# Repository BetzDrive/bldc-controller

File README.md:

# Getting Started
```bash
cd ~
git clone https://github.com/BetzDrive/bldc-controller.git
cd bldc-controller
sudo apt-get install gdb-multiarch python3-pip
make setup
```

### Testing
A quick way of running the full test suite is to use `make test`. This will lint and run any code testing.

### Compiling
```bash
bazel build //<bootloader or firmware>
```

### Uploading via ST-LINK
```bash
bazel run //<bootloader or firmware>:flash
```

### Debugging via ST-LINK
To debug during execution, you can attach the debugger at any time using the following code. Keep in mind this is done with a direct connection to the hardware via an ST-Link.
```bash
# First terminal (flash latest and start gdb multiarch)
bazel run //<bootloader or firmware>:flash
bazel run //<bootloader or firmware>:gdb
# Second terminal (start openocd server)
bazel run //<bootloader or firmware>:debug
```

### Upload firmware via RS485
```bash
bazel run //firmware:upload
```

### Upload bootloader via RS485
Use this with caution. If this fails and a power cycle or reboot occurs, the board will have to be programmed directly. In the case of a failed upload, disable the enumeration procedure and try again with the same board ID. To be safe, first upload and test on an easy-to-remove link such as the gripper or base which are not as difficult to access in case of a failure.

```bash
bazel run //bootloader:upload
```

### Serial Transmission Speed Limits
USB Serial device drivers only permit at most one transmission per millisecond. By default, this is set to 16 milliseconds on our usb to RS485 converters. To change this execute the following terminal commands:

```bash
cat /sys/bus/usb-serial/devices/ttyUSB<id_num>/latency_timer
setserial /dev/ttyUSB<id_num> low_latency
cat /sys/bus/usb-serial/devices/ttyUSB<id_num>/latency_timer
```

(when running the arm, this is done automatically by the ROS control stack)

# Python Scripts
These scripts are made to remotely interface with the boards. They can debug, program, and run the boards. They interface using our custom communications protocol. The scripts are grouped under the base command `bdt`. Read more with `bdt -h`.

### Motor Calibration
To calibrate the motor board, a motor must first be attached without a load for optimal calibration. The results of calibration are based on the properties of the given motor.

* `bdt calibrate_encoder <serial_port> <board_id> <duty_cycle>`
* `bdt upload_calibration <serial_port> <board_id>`

1. Run _calibrate_encoder_: for 24V Power Supplies the duty cycle used in testing is 0.3 and for 48V or 50V supplies use half (0.15). This will generate a file called calibrations.json
2. Run _upload_calibration_ with the updated calibrations.json and the generated file will be loaded onto the board.

After completing these steps, the motor should be controllable.

### Update Motor Calibration Constants (PID and Limits)
Run this script after there's a calibration on the board. Modify the contents of the script to adjust tunings!

`bdt update_calibration <serial_port> <board_id>`

### Motor Control
Use this script to spin a motor with a given current command. A substantial starting point is 0.5 and increase above this with proper supervision! A negative command will reverse the direction. Description of what arguments each mode takes can be found with the '-h' option.

`bdt control_motor <serial_port> <board_id> <mode> <command>`

To control multiple motors,

```
bdt control_motor <serial_port> 1,2,3 torque 0.5,0.25,0
bdt control_motor <serial_port> 1,2,3 current [0,0.5],[0,0.25],[0,0]
```

### Read Sensor
This script lets a user read from any of the sensors on-board the device.

`bdt read_sensor <serial_port> <board_ids> <sensor>`

### View Control Loop
Plots the control target and the resulting quadrature/direct current commands. This is low frequency so use the recorder to get a better sense of the internal state of the motor driver.

### Recording
These scripts start and read off an on-board buffer of the commutation at each control cycle. There are included plotting scripts. This interfaces directly with the Recorder class in the firmware.

# System Design
The BLDC is built on ChibiOS. The operating system allows for quick development and thread management which have been useful for this fast-paced project. To supplement missing features, the STM32 library has been included. Memory is allocated primarily for firmware though two blocks are used to store the calibration and board id (refer to section 3.3 of [reference manual](https://www.st.com/content/ccc/resource/technical/document/reference_manual/3d/6d/5a/66/b4/99/40/d4/DM00031020.pdf/files/DM00031020.pdf/jcr:content/translations/en.DM00031020.pdf "STM32F4 Reference Manual") for memory).

## Common
In both firmware and bootloader, the primary system is the communication code. This is designed to allow users to read/write variables as well as reprogram the board remotely. When a board receives a packet, a small green LED will blink to indicate it has identified the message.

## Bootloader [Flash Sector 0]
This small system is primarily meant as a method to allow updates of the firmware without a programmer. On command, it will move the program counter to the start of the firmware code.

### LED Indicator
During normal operation, the bootloader will pulse the RGB LED blue.

## Board ID [Flash Sector 1]
To keep track of the board ID when switching between firmware and bootloader, and in case of a system fault, the board id is stored in flash.

## Calibrations [Flash Sector 2]
To keep calibrations between restarts, a section of flash is reserved and loaded to/from by firmware. Once a calibration is stored, it will load on boot without host intervention. To modify the calibration, either re-calibrate the motor or use the `update_calibration.py` tool.

## Firmware [Flash Sectors 4 - 11]
The firmware code starts by initializing hardware devices and then splits into a number of threads.

### LED Indicator [low priority]
During normal operation, the firmware will pulse the RGB LED green. If a red or blue pulse is seen while in firmware, the driver chip Fault and/or OTW pins have activated. Refer to the DRV8312 datasheet for the type of fault.

### Sensor Thread [low priority]
Pulls updates from the accelerometer and temperature sensor.
  
### Communication Thread [normal priority]
Used to update motor targets and read current position, velocity, accelerometer data, temperature, etc.

### Control Thread [high priority]
Pulls updates from ADC for current/voltage measurements as well as queues reads to the absolute encoder. With this data, FOC is computed with output duty cycles to STM32 timing hardware.
  
### Independent Watchdog Thread [high priority]
Used to keep the system live while protecting from the chance of a hard fault or any other unforseen errors. When a lock-up occurs, the system will reset into bootloader which will then check the watchdog reset flag. If it is active, the bootloader will return the system to firmware mode.

# Modifying Pins
All of the code can be directly modified except for the pins (althought you can technically modify it directly too). To allow for the pin definitions and defaults to be auto-generated and easily maintained, please make any modifications in [ChibiStudio](https://osdn.net/projects/chibios/) and generate new pin files from the studio interface.

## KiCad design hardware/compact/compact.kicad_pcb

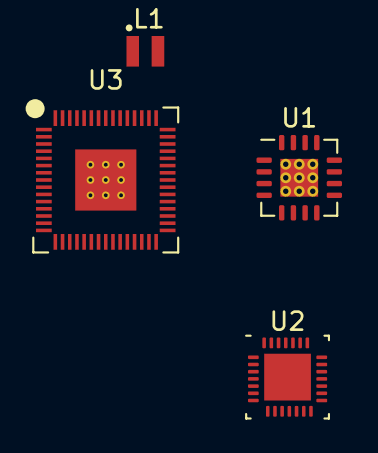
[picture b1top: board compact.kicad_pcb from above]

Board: 2 copper layers, 4 parts (0 on the bottom side), 6 nets, no tracks yet.

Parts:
L1: 3.3uH; L_pol_2016
U1: QFN-16-1EP_4x4mm_P0.65mm_EP2.1x2.1mm_ThermalVias
U2: WQFN-28-1EP_2.6x2.6mm_P0.6mm_EP2.4x2.4mm
U3: RP2350A-QFN60; RP2350A_QFN-60_EP_7.75x7.75_Pitch0.4mm

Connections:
+3V3: L1.1, U1.14 (VS), U1.15 (VS), U2.1 (PVDD), U3.1 (IOVDD), U3.6 (DVDD), U3.11 (IOVDD), U3.20 (IOVDD), U3.23 (DVDD), U3.30 (IOVDD), U3.38 (IOVDD), U3.39 (DVDD), U3.44 (ADC_AVDD), U3.45 (IOVDD), U3.46 (VREG_AVDD), U3.49 (VREG_VIN), U3.50 (VREG_FB), U3.53 (USB_OTP_VDD), U3.54 (QSPI_IOVDD)
GND: U1.6 (GND), U1.7 (GND), U2.4 (GVDD), U2.28 (GND), U3.47 (VREG_PGND), U3.61 (GND)
unnamed: U1.16 (OUT1), U3.40 (GPIO26_ADC0)
unnamed: U1.5 (OUT2), U3.41 (GPIO27_ADC1)
unnamed: U1.13 (OUT3), U3.42 (GPIO28_ADC2)
unnamed: L1.2, U3.48 (VREG_LX)

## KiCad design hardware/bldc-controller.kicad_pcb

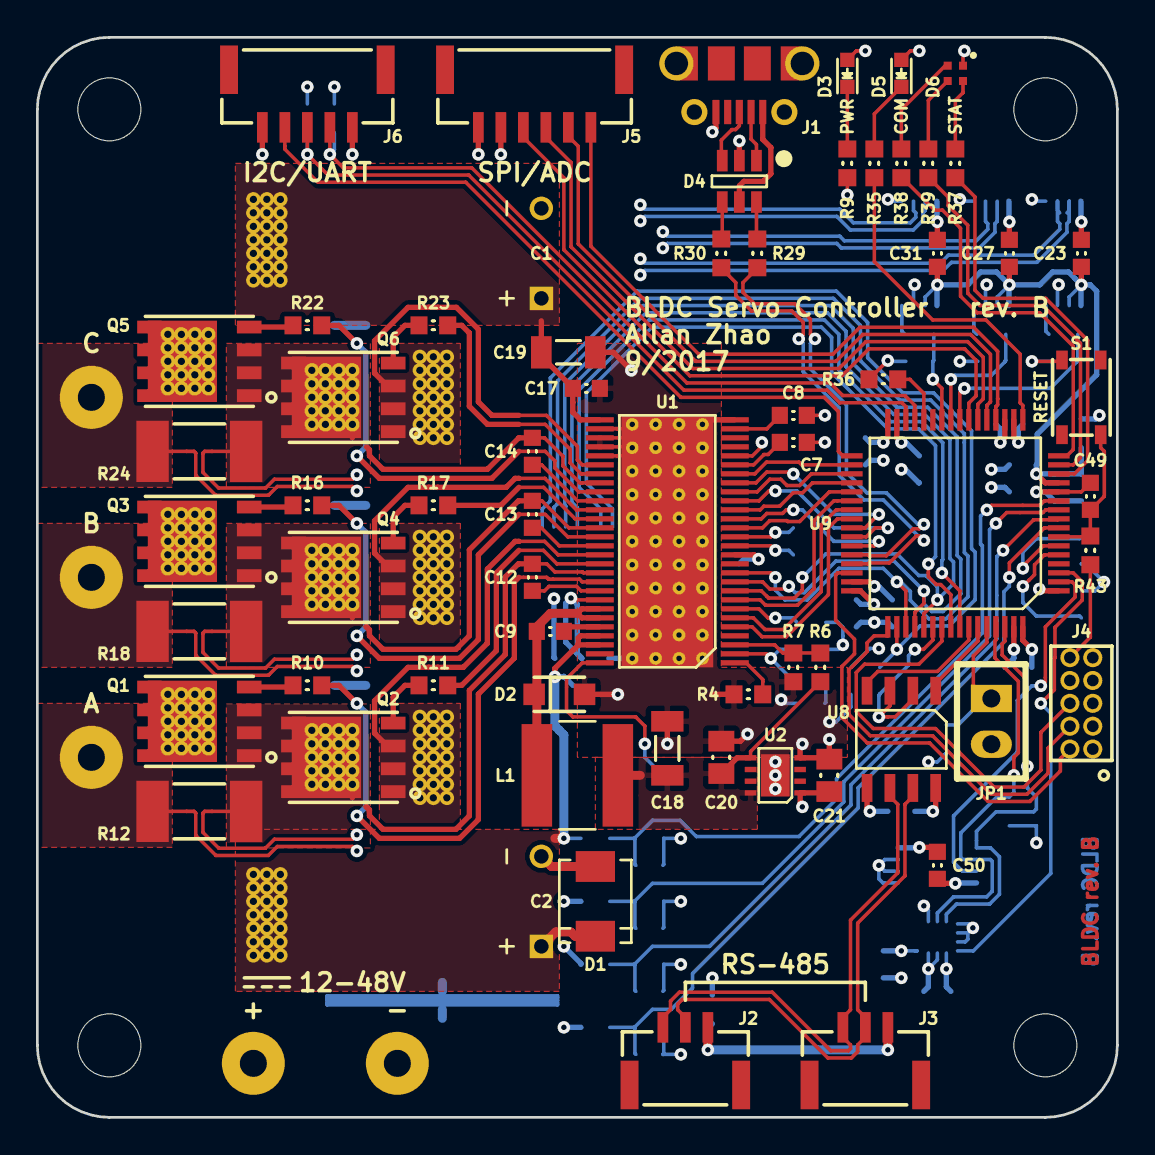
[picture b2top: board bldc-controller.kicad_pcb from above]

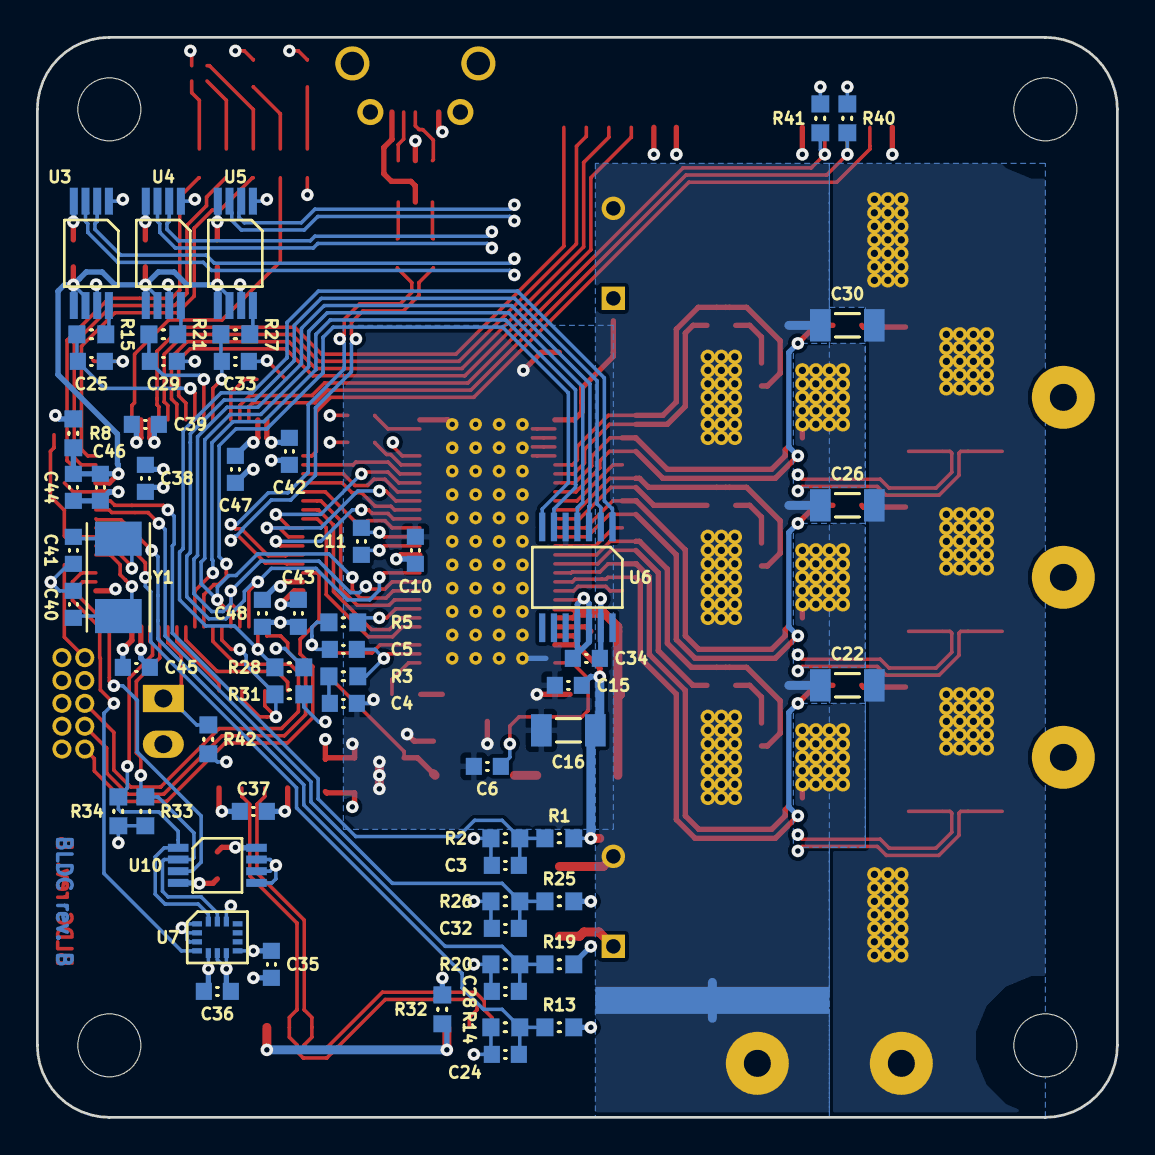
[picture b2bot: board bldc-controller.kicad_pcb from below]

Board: 4 copper layers, 60.0 x 60.0 mm, 140 parts (62 on the bottom side), 119 nets.

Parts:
C1, C2: 330u; C_Radial_D10_L26.5_P5_Horizontal
C3, C9, C12, C13, C14, C15, C17, C23, C27, C31, C34, C35, C36, C37, C39, C42, C43, C45, C46, C49, C50: 0.1u; C_0603_IPC_NOMINAL
C4: 6.8n; C_0603_IPC_NOMINAL
C5: 120p; C_0603_IPC_NOMINAL
C6: 1n; C_0603_IPC_NOMINAL
C7, C8, C44: 1u; C_0603_IPC_NOMINAL
C10, C47, C48: 2.2u; C_0603_IPC_NOMINAL
C11: 22n; C_0603_IPC_NOMINAL
C16, C19: 4.7u; C_1206_IPC_NOMINAL
C18: 47u; C_1206_IPC_NOMINAL
C20, C21: 10u; C_0805_IPC_NOMINAL
C22, C26, C30: 2.2u; C_1206_IPC_NOMINAL
C24, C28, C32: DNP; C_0603_IPC_NOMINAL
C25, C29, C33: 10n; C_0603_IPC_NOMINAL
C38: 4.7u; C_0603_IPC_NOMINAL
C40, C41: 27p; C_0603_IPC_NOMINAL
D1: SMBJ48D; DO-214AA
D2: PMEG6020ER; SOD123W
D3: Green; LED_0603
D4: ESD_DIODES; SOT23-6L
D5: Yellow; LED_0603
D6: RGB; SMLP34RGB
J1: USB_MICRO_B; 105017-0001
J2, J3: JST GH; SM03B-GHS-TB
J4: 1.27mm Pin Header; 62201021121
J5: JST GH; SM06B-GHS-TB
J6: JST GH; SM05B-GHS-TB
JP1: Pin Header; CONN-100MIL-M-1x2
L1: 33u; TYS6045
P1, P2, P3, P4, P5: Solder Terminal; SOLDER_HOLE_1.5MM
Q1, Q2, Q3, Q4, Q5, Q6: CSD18533; Q5B
R1, R13, R19, R25: 39.2k; R_0603_IPC_NOMINAL
R2, R14, R20, R26: 2.21k; R_0603_IPC_NOMINAL
R3: 15k; R_0603_IPC_NOMINAL
R4: 220k; R_0603_IPC_NOMINAL
R5, R8: 0; R_0603_IPC_NOMINAL
R6: 52.3k; R_0603_IPC_NOMINAL
R7: 10k; R_0603_IPC_NOMINAL
R9: 200; R_0603_IPC_NOMINAL
R10, R11, R16, R17, R22, R23: 4.7; R_0603_IPC_NOMINAL
R12, R18, R24: 0.002; CSS2H-2512
R15, R21, R27: 100; R_0603_IPC_NOMINAL
R28, R31, R36, R42: 47k; R_0603_IPC_NOMINAL
R29, R30: 22; R_0603_IPC_NOMINAL
R32: DNP; R_0603_IPC_NOMINAL
R33, R34, R40, R41: 4.7k; R_0603_IPC_NOMINAL
R35: 120; R_0603_IPC_NOMINAL
R37: 180; R_0603_IPC_NOMINAL
R38: 150; R_0603_IPC_NOMINAL
R39: 62; R_0603_IPC_NOMINAL
R43: 1k; R_0603_IPC_NOMINAL
S1: SW_Push_4P; PTS_810
U1: DRV8301; R-PDSO-G56-STRICT
U2: AP7361C; U-DFN3030-8
U3, U4, U5: INA240A2; TSSOP-8
U6: AS5047D; TSSOP-14
U7: LSM6DS3US; LGA-14L-STRICT
U8: ST3485; SOIC-8
U9: STM32F405R; LQFP-64
U10: LM75B; TSSOP-8
Y1: 8 MHz; ABM7
Z1: NET_TIE; WIDE_NET_TIE
Z2, Z5, Z8: NET_TIE; NET_TIE_0.3MM
Z3, Z4, Z6, Z7, Z9, Z10: NET_TIE; NET_TIE_8mil

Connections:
/Encoder/A: U6.7, U9.56
/Encoder/B: U6.6, U9.57
/Encoder/CLK: U1.11, U6.2, U9.51
/Encoder/CSN: R28.2, U6.1, U9.50
/Encoder/MISO: U1.10, U6.3, U9.52
/Encoder/MOSI: U1.9, U6.4, U9.53
/Gate Driver, Power/5V: C18.1, C20.1, L1.2, R6.1, U2.5, U2.8
/Gate Driver, Power/EN_GATE: U1.16, U9.37
/Gate Driver, Power/INH_A: U1.17, U9.43
/Gate Driver, Power/INH_B: U1.19, U9.42
/Gate Driver, Power/INH_C: U1.21, U9.41
/Gate Driver, Power/INL_A: U1.18, U9.36
/Gate Driver, Power/INL_B: U1.20, U9.35
/Gate Driver, Power/INL_C: U1.22, U9.34
/Half Bridge A/GH: R10.1, U1.47
/Half Bridge A/GL: R11.1, U1.45
/Half Bridge A/ISENSE_IN+: U3.2, Z3.1
/Half Bridge A/ISENSE_IN-: U3.3, Z4.1
/Half Bridge A/PHASE: P3.1, R12.2, R13.1, Z4.2
/Half Bridge A/SH: C12.1, Q1.S, Q2.D, R12.1, U1.46, Z3.2
/Half Bridge A/SL: U1.44, Z2.2
/Half Bridge B/GH: R16.1, U1.42
/Half Bridge B/GL: R17.1, U1.40
/Half Bridge B/ISENSE_IN+: U4.2, Z6.1
/Half Bridge B/ISENSE_IN-: U4.3, Z7.1
/Half Bridge B/PHASE: P4.1, R18.2, R19.1, Z7.2
/Half Bridge B/SH: C13.1, Q3.S, Q4.D, R18.1, U1.41, Z6.2
/Half Bridge B/SL: U1.39, Z5.2
/Half Bridge C/GH: R22.1, U1.37
/Half Bridge C/GL: R23.1, U1.35
/Half Bridge C/ISENSE_IN+: U5.2, Z9.1
/Half Bridge C/ISENSE_IN-: U5.3, Z10.1
/Half Bridge C/PHASE: P5.1, R24.2, R25.1, Z10.2
/Half Bridge C/SH: C14.1, Q5.S, Q6.D, R24.1, U1.36, Z9.2
/Half Bridge C/SL: U1.34, Z8.2
/ISENSE_A: C25.1, R15.2, U9.24
/ISENSE_B: C29.1, R21.2, U9.25
/ISENSE_C: C33.1, R27.2, U9.26
/Microcontroller/I2C_SCL: R33.2, U7.13, U9.61, U10.2
/Microcontroller/I2C_SDA: R34.2, U7.14, U9.62, U10.1
/Microcontroller/IMU_INT1: U7.4, U9.3
/Microcontroller/MDRV_NFAULT: U1.6, U9.39
/Microcontroller/MDRV_NOCTW: U1.5, U9.40
/Microcontroller/MDRV_NSCS: U1.8, U9.38
/Microcontroller/NRST: J4.10, R43.2
/Microcontroller/PA4: J5.1, U9.20
/Microcontroller/PA5: J5.2, U9.21
/Microcontroller/PA6: J5.3, U9.22
/Microcontroller/PA7: J5.4, U9.23
/Microcontroller/PB10: J6.2, R41.2, U9.29
/Microcontroller/PB11: J6.3, R40.2, U9.30
/Microcontroller/PB12: J6.4, U9.33
/Microcontroller/SWCLK: J4.4, U9.49
/Microcontroller/SWDIO: J4.2, U9.46
/Microcontroller/SWO: J4.6, U9.55
/RS-485/D+: J2.2, J3.2, U8.7
/RS-485/D-: J2.1, J3.1, U8.6
/RS-485/DE: R31.1, U8.2, U8.3, U9.54
/RS-485/DI: U8.4, U9.58
/RS-485/RO: U8.1, U9.59
/Temperature Sensor/OS: U9.2, U10.3
/USB/D+: R30.1, U9.45
/USB/D-: R29.1, U9.44
/USB/VBUS: D4.5, J1.1
/VSENSE_A: C24.1, R13.2, R14.1, U9.8
/VSENSE_B: C28.1, R19.2, R20.1, U9.9
/VSENSE_C: C32.1, R25.2, R26.1, U9.10
/VSENSE_VIN: C3.1, R1.2, R2.1, U9.11
GND: C3.2, C4.2, C5.2, C6.2, C7.2, C8.2, C10.1, C15.2, C16.2, C17.2, C18.2, C19.2, C20.2, C21.2, C23.1, C24.2, C25.2, C27.1, C28.2, C29.2, C31.1, C32.2, C33.2, C34.2, C35.2, C36.2, C37.1, C38.2, C39.2, C40.1, C41.1, C42.2, C43.2, C44.2, C45.2, C46.2, C47.1, C48.1, C49.1, C50.2, D2.2, D4.2, J1.5, J4.3, J4.5, J5.6, J6.5, P2.1, R2.2, R4.1, R5.1, R7.2, R9.2, R14.2, R20.2, R26.2, R31.2, R32.1, R36.2, R42.2, S1.2, U1.28, U1.30, U1.31, U1.32, U1.33, U1.57, U2.4, U2.9, U3.1, U3.4, U3.7, U4.1, U4.4, U4.7, U5.1, U5.4, U5.7, U6.5, U6.13, U7.1, U7.2, U7.3, U7.6, U7.7, U8.5, U9.12, U9.18, U9.63, U10.4, U10.5, U10.6, U10.7, Z1.1
GNDPWR: C1.2, C2.2, C22.2, C26.2, C30.2, D1.2, Q2.S, Q4.S, Q6.S, Z1.2, Z2.1, Z5.1, Z8.1
unnamed: C4.1, R3.2
unnamed: C5.1, R3.1, U1.2
unnamed: C6.1, U1.56
unnamed: C7.1, U1.23
unnamed: C8.1, U1.27
unnamed: C9.1, D2.1, L1.1, U1.50, U1.51
unnamed: C9.2, U1.52
unnamed: C10.2, U1.13
unnamed: C11.1, U1.15
unnamed: C11.2, U1.14
unnamed: C12.2, U1.48
unnamed: C13.2, U1.43
unnamed: C14.2, U1.38
unnamed: C40.2, U9.5, Y1.1
unnamed: C41.2, U9.6, Y1.2
unnamed: C47.2, U9.31
unnamed: C48.2, U9.47
unnamed: C49.2, R43.1, S1.3, U9.7
unnamed: D3.1, R9.1
unnamed: D4.1, J1.2
unnamed: D4.3, J1.3
unnamed: D4.4, R30.2
unnamed: D4.6, R29.2
unnamed: D5.1, R35.1
unnamed: D6.KB, R39.1
unnamed: D6.KG, R38.1
unnamed: D6.KR, R37.1
unnamed: J2.3, J3.3, R32.2
unnamed: JP1.1, R42.1, U9.60
unnamed: Q1.G, R10.2
unnamed: Q2.G, R11.2
unnamed: Q3.G, R16.2
unnamed: Q4.G, R17.2
unnamed: Q5.G, R22.2
unnamed: Q6.G, R23.2
unnamed: R4.2, U1.1
unnamed: R5.2, U1.7
unnamed: R6.2, R7.1, U1.3
unnamed: R15.1, U3.8
unnamed: R21.1, U4.8
unnamed: R27.1, U5.8
unnamed: R35.2, U9.17
unnamed: R36.1, U9.28
unnamed: R37.2, U9.14
unnamed: R38.2, U9.16
unnamed: R39.2, U9.15
VDD: C21.1, C34.1, C35.1, C36.1, C37.2, C38.1, C39.1, C42.1, C43.1, C45.1, C50.1, D3.2, D5.2, D6.A, J4.1, J5.5, J6.1, JP1.2, R8.1, R28.1, R33.1, R34.1, R40.1, R41.1, U1.24, U1.49, U2.1, U6.11, U6.12, U7.5, U7.8, U7.12, U8.8, U9.1, U9.19, U9.32, U9.48, U9.64, U10.8
VDDA: C23.2, C27.2, C31.2, C44.1, C46.1, R8.2, U3.5, U3.6, U4.5, U4.6, U5.5, U5.6, U9.13
VIN: C1.1, C2.1, C15.1, C16.1, C17.1, C19.1, C22.1, C26.1, C30.1, D1.1, P1.1, Q1.D, Q3.D, Q5.D, R1.1, U1.29, U1.53, U1.54

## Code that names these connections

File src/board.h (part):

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 * PA1  - LED_B                     (alternate 2).
 * PA2  - LED_G                     (alternate 2).
 * PA3  - LED_Y                     (output pushpull maximum).
 * PA4  - PIN4                      (input pullup).
 * PA5  - PIN5                      (input pullup).
 * PA6  - PIN6                      (input pullup).
 * PA7  - PIN7                      (input pullup).
 * PA8  - MDRV_INH_C                (alternate 1).
 * PA9  - MDRV_INH_B                (alternate 1).
 * PA10 - MDRV_INH_A                (alternate 1).
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/*
 * GPIOB setup:
 *
 * PB0  - ISENSE_C                  (analog).
 * PB1  - PIN1                      (input pullup).
 * PB2  - PIN2                      (input pulldown).
 * PB3  - SWO                       (alternate 0).
 * PB4  - ENC_A                     (input pullup).
 * PB5  - ENC_B                     (input pullup).
 * PB6  - RS485_TX                  (alternate 7).
 * PB7  - RS485_RX                  (alternate 7).
 * PB8  - I2C_SCL                   (alternate 4).
 * PB9  - I2C_SDA                   (alternate 4).
 * PB10 - PIN10                     (input pullup).
 * PB11 - PIN11                     (input pullup).
 * PB12 - PIN12                     (input pullup).
 * PB13 - MDRV_INL_C                (alternate 1).
 * PB14 - MDRV_INL_B                (alternate 1).
 * PB15 - MDRV_INL_A                (alternate 1).
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/*
 * GPIOC setup:
 *
 * PC0  - VSENSE_A                  (analog).
 * PC1  - VSENSE_B                  (analog).
 * PC2  - VSENSE_C                  (analog).
 * PC3  - VSENSE_VIN                (analog).
 * PC4  - ISENSE_A                  (analog).
 * PC5  - ISENSE_B                  (analog).
 * PC6  - MDRV_EN                   (output pushpull maximum).
 * PC7  - MDRV_NSCS                 (output pushpull maximum).
 * PC8  - MDRV_NFAULT               (input pullup).
 * PC9  - MDRV_NOCTW                (input pullup).
 * PC10 - SPI_CLK                   (alternate 6).
 * PC11 - SPI_MISO                  (alternate 6).
 * PC12 - SPI_MOSI                  (alternate 6).
 * PC13 - TEMP_INT                  (input pullup).
 * PC14 - IMU_INT1                  (input pullup).
 * PC15 - PIN15                     (input pullup).
 */
#define VAL_GPIOC_MODER             (PIN_MODE_ANALOG(GPIOC_VSENSE_A) |      \
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
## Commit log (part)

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2018-07-15 Refactored comms code
    - commsRegAccessHandler now directly returns number of bytes read/written, instead of by reference
    - more consistency: all calls to handleVarAccess use buf_size
    - note: all registers allow r/w now, including result registers
    - fixed some compiler warnings
2018-07-27 added stm32cubemx project
2018-07-30 Adding lift test code. (Not yet complete)
2018-08-02 Initial commit of new stm32cubemx project for electrical test of BLDC board.
2018-08-02 Added ADC read functionality.
2018-08-02 Moved initialization code so it doesn't get overwritten by cube.
2018-08-02 PWM seems to be working now.
2018-08-03 Cleared all outputs to BLDC driver.
2018-08-03 SPI testing code works, though only one of the boards seems to work with it.
2018-08-13 Adding config file changes for motor controller
2018-08-15 Adding initial movement command to prevent lockup problem
2018-08-15 Copying old drivers and slowly converting to operate properly
2018-09-04 Setup encoder and motor drivers. Including code for caching data on-board and returning it to host
2018-09-04 Setting all control and torque constants to zero
2018-09-05 SPI phase is set to 2EDGE
2018-10-01 Adding acelerometer reading script
2018-10-10 Adding final changes and gain adjustments for working FOC w/current sense
2018-10-30 I believe this was being modified to allow testing of just PWM output for noise characterization.
2018-11-01 fixing duty_cycle.py naming
2018-11-29 Adding support for Disco Bus
2018-12-20 Backtracking some accidental additions to the prior commit
2018-12-23 Updating IMU to include resource management and test script to interface with PV3
2019-01-17 Cleaning up code and removing white space
2019-01-23 Minor adjustments to test scripts
2019-01-29 Simpliflying state
2019-01-29 Updating ivsense constants and averaging algorithm
2019-01-31 Adding update to constant calculation and fixed offest bug
2019-02-07 Adding changes to motor calibration scripts
2019-02-14 Flipping start order of timers and removing duty cycle scaling
2019-03-06 Adding enumerate support to more tools
2019-03-14 Adding better support for enumerated board setup
2019-04-11 Fixing unpacking issue for enumeration on client
2019-04-17 Floating disco bus pins to support new decoupling hardware
2019-04-17 Adjusting submodule to group submodule
2019-04-24 Fixed log?
2019-04-29 Taking out of sub-folders (path issues with comms.py)
2019-04-29 Adjusting documentation to account for new hardware changes!
2019-05-02 Rolling back to stable feed-forward!
2019-05-02 Adding multi-board reading fix
2019-05-07 Add guidance to install appropriate gdb
2019-05-09 Peripheral initialization mods
    - Remap ADC channels so isns happens first
    - Change to edge aligned PWM
    - Make TIM3 function as a delay between PWM and ADC sampling
2019-05-09 Scale all duty cycle commands to enforce 0.9 as maximum duty cycle
2019-05-09 Adjust current sensing constants
    - Removes the 1.5A offset, but not 100% confident in these numbers, need double checking
2019-05-16 Adding changes pertaining to the flash sector issue
2019-05-18 Re-adding current control and updating logging firmware
2019-05-19 Adding support for EAC and making calibrations easier to work with!
2019-05-19 Adding stuff for calibration with current offset
2019-05-19 Some small changes for offsets
2019-05-21 Splitting errors into two different colored lights
2019-05-24 Adjusting help menu and renaming to make info clearer for controlling the motors
2019-05-28 Adding Live Graph Plotting
2019-05-28 Disable gates by default to reset driver chip in case of latching fault
2019-05-28 Setting current limit to a defined constant
2019-05-30 Added in-progress fixes for current control
2019-06-04 Adding test scrip to send/receive between two RS485-USB devices
2019-06-04 Adding more debug for comms!
2019-06-05 Adjusting timeout as was unable to read full packets before timeout
2019-06-05 Re-enabling initialize
2019-06-06 Changing OTW warning to blue flashing light
2019-06-06 Fixing last commit related to theta inverse
2019-06-06 New PID library! With some additional corrections to current reads.
2019-06-06 Adding low and high frequency velocity estimations.
2019-06-11 Tools update for multi-mode control and firmware update for windup fix
2019-06-19 Terminating resistor code/doc update
2019-06-19 Adding openocd config for debugging
2019-06-21 Cleaning up comms a little
2019-06-21 Reducing wait times and moving old file
2019-06-25 Working towards calibration rework
2019-06-25 Changes to support reboot on firmware crash
2019-06-26 Added tools to download jsons calibrations from old firmware and adjusted upload/calibration script to support the format
2019-06-28 Updates to driver chip reset after fault, IWDG timeout, default control mode, flash verification of calibration reads, and thread priorities
2019-07-01 Tidying up
2019-07-02 Adding experimental mutexes
2019-07-02 Increasing storage to uint32_t to avoid overflow
2019-07-02 Fast sqrt
2019-07-04 Adjusting current control back up to 20kHz (system can operate fully at this speed).
2019-07-08 Compiles to same source on compiler explorer (thought it might be more efficient)
2019-07-10 Completed and tested namespaces
2019-07-17 Reducing number of globals with local statics, improving names, new control mode
2019-07-18 Documentation, comms, watchdog reset notification, and minor tool updates
2019-07-19 Small info additions to tools
2019-07-25 Start of data collection scripts
2019-07-25 Default control to high-impedance when losing comms
2019-08-02 Improving print statements of upload scripts
2019-08-14 int16_t not uint16_t!
2019-08-21 Working towards better position control
2019-08-22 Changing d term calc for PID
2019-08-23 Position interpolation code!
2019-08-28 More small adjustments
2019-09-23 Missed small change to make compile...
2019-09-23 Remapped all pins for v2 boards
2019-09-28 Clearing the timeout flag...
2019-10-03 Cleaning up warnings
2019-10-15 Moving DMA Stream for SPI3 to prevent overlap with I2C2 and correcting LED colors
2019-11-11 Adjusting constants/config for new boards
2019-11-11 GDB Multiarch replaced specific gdb versions
2019-11-11 Tools update for v2 boards
2019-11-12 Fixed ADC parameters for new board revision
2019-11-12 More consistency in ADC channels
2019-11-13 Recorder updates
2019-11-13 Changed to center aligned PWM.
    While the frequency constant was doubled because of the center aligned feature the PWM will still be at 20kHz frequency
2019-11-13 Updated recorder element count
2019-11-15 Revert "Changed ADC sampling to be relative to falling edge instead of PWM center"
    This reverts commit a06cbe19c0f1e92e3d5ec617d9e5343458775861.
2019-11-18 More conservative delay for bootloader exit
2019-11-20 Fixed current readings for low PWM duty cycles
    Clamped PWM duty cycle between 0.05 and 0.95, added simultaneous
    sampling of all the current channels
2020-01-21 imu test now produces correct gravity scaled vector
2020-03-03 Support for Hardware Version 2.2 (#27)
    * Remapped all pins for v2 boards
    * Moving DMA Stream for SPI3 to prevent overlap with I2C2 and correcting LED colors
    * Moving old imu driver
    * Adjusting constants/config for new boards
    * Driver Updates (Not working fully yet but avoids address collision)
    * GDB Multiarch replaced specific gdb versions
2020-07-24 Better names/makefiles
2020-08-17 Use common make imports for bootloader
2020-09-06 update read_sensor
2020-09-07 add debug script
2020-09-13 Flash read/write fixes
2020-10-04 Adjusting max duty cycle.
2021-03-10 More python3 support and improved stability of tools.
2021-03-11 Whitespace and formatting adjustments.
2021-03-11 Whitespace and Style Cleanup (#33)
    * Swap file deletion in chibios repo
    * Whitespace and formatting adjustments.
2021-03-11 Fix exception handling
2021-03-11 Clang formatting and 80 char line limiting.
2021-03-12 Actual clang formatter.
2021-03-12 Add CI for cpplint
2021-03-12 Bootloader linting
2021-03-12 Updating ci to include common
2021-03-12 Firmware linting
2021-03-13 Compiling CI
2021-03-13 More compile debug
2021-03-13 Missed tab
2021-03-16 Adope bldc-controller as the workspace folder
2021-04-07 Adding error rate to control_motor.py printout
2021-04-11 Initial board/argparse adjustments
2021-04-17 Formatting, WDG Reset, and updating read_sensor
2021-05-17 First unit test
2021-05-17 Test description
2021-05-17 Renaming to test for all tools
2021-05-17 Calibrate Encoder test
2021-05-17 Update Calibration and fix file writing when testing calibrate encoder
2021-05-17 Add pytest to workflows
2021-05-17 No support for python 3.5/3.6 and adding numpy to dependencies
2021-05-17 add matplotlib to reqs
2021-05-19 Switch default mocking to fixture
2021-05-20 Make bd_tools package to enable testing and runtime to work
2021-05-20 Small bug fixes from real world testing
2021-05-20 Auto-formatting python
2021-05-20 Line length is 79 for flake8
2021-05-21 Add lint check to workflow
2021-05-21 Updated to fix black/isort integration
2021-05-21 Move deprecated tool to dev
2021-05-24 Typo fix
2022-05-14 Fix install command
2022-05-15 Make bd_tools accessible through one interface
2022-05-15 Lock down click version
2022-05-15 Make bd_tools accessible through one interface (#43)
    * Make bd_tools accessible through one interface
    * Run linting with python3.8
    * Lock down click version
    * Remove unecessary code
2022-05-15 Fix sub-args
2022-06-26 Minor progress on protocol parsing utility
2022-06-26 Immensely improve uart performance by maximizing uart irq priority (#45)
2022-06-26 Nanopb submodule
2022-06-27 Upload convenience function for single driver development (#46)
2022-07-04 Replace calibrations internally with proto based calibrations
2022-07-04 Use protobuf for calibrations (#47)
    * Nanopb submodule
    * Create calibration proto
    * Replace calibrations internally with proto based calibrations
    * Upload convenience function for single driver development
    * Generate protos and compile in same make instance
2022-07-07 Reduce argparse code duplication
2022-07-08 Enable velocity control; write calibrations as pbs (#48)
    This is a two part commit.
    1. Switches the calibration storage system to use protobufs
    2. Finishes off velocity control with gains for small motors
2022-07-08 Relocate submodules to third party dir (#50)
    Moves nanopb and chibios to dedicated directory.
    Adjusts build system and user setup process.
2022-07-12 Build bootloader with bazel (#52)
2022-07-12 Github CI bazel compile target (#53)
2022-08-15 Firmware builds in bazel (#54)
2022-08-16 [Bazel] Motor controller execution successful
2022-08-16 [Bazel] Rename build files
2022-08-16 [Bazel] Rename build files (#56)
2022-08-16 [Bazel] Remove redundant flags and compile for speed (#57)
2022-08-18 [Cleaning] Reduce clutter in root directory
2022-08-18 [Buildsystem] Remove makefiles
2022-08-21 [Debug] Documentation and debug tools update
2022-08-21 [Re-org] Minor improvements and documentation
2022-08-21 [Re-org] Move drivers out of firmware (#61)
2022-08-21 [Drivers] Move old drivers to new dir
2022-08-21 [Drivers] Relocate old drivers (#63)
    * [Drivers] Move old drivers to new dir
    * [Drivers] Formatting old drivers
2022-08-21 [Time] Add usec time and validation tool (#64)
2022-09-05 [Bdt] Fix enumeration bug
2022-09-06 [Bdt] Fix flags read error
    Topic: flags_error_fix
2022-09-06 [Bdt] Error code summaries for each loop
2022-09-13 [Bdt] Fix enumeration bug (#65)
    Topic: delay_on_enumeration
2022-09-13 [Tools] Improve tool help formatting
    Topic: tools_help_formatting
2022-09-26 [Bdt] Switch to dcargs
    Topic: bdt_uses_dcargs
    Reviewers: brent
2024-06-09 [Sim] Rust attempt
2024-12-22 [Compact] Betz compact PCB WIP
2025-01-13 [ThirdParty] Bump bazel-embedded version
    Topic: bump_bazel_embedded
2025-04-26 [Comms] Some initial motor moving
2025-04-27 [Hack] bazelrc for desktop
2025-06-27 [Infra] More work to try to add toolchains for cross compilation as a transition
2026-02-14 [Comms] Write a new motor comms master

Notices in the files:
src/board.h:
ChibiOS/RT - Copyright (C) 2006-2013 Giovanni Di Sirio
Licensed under the Apache License, Version 2.0 (the "License");
